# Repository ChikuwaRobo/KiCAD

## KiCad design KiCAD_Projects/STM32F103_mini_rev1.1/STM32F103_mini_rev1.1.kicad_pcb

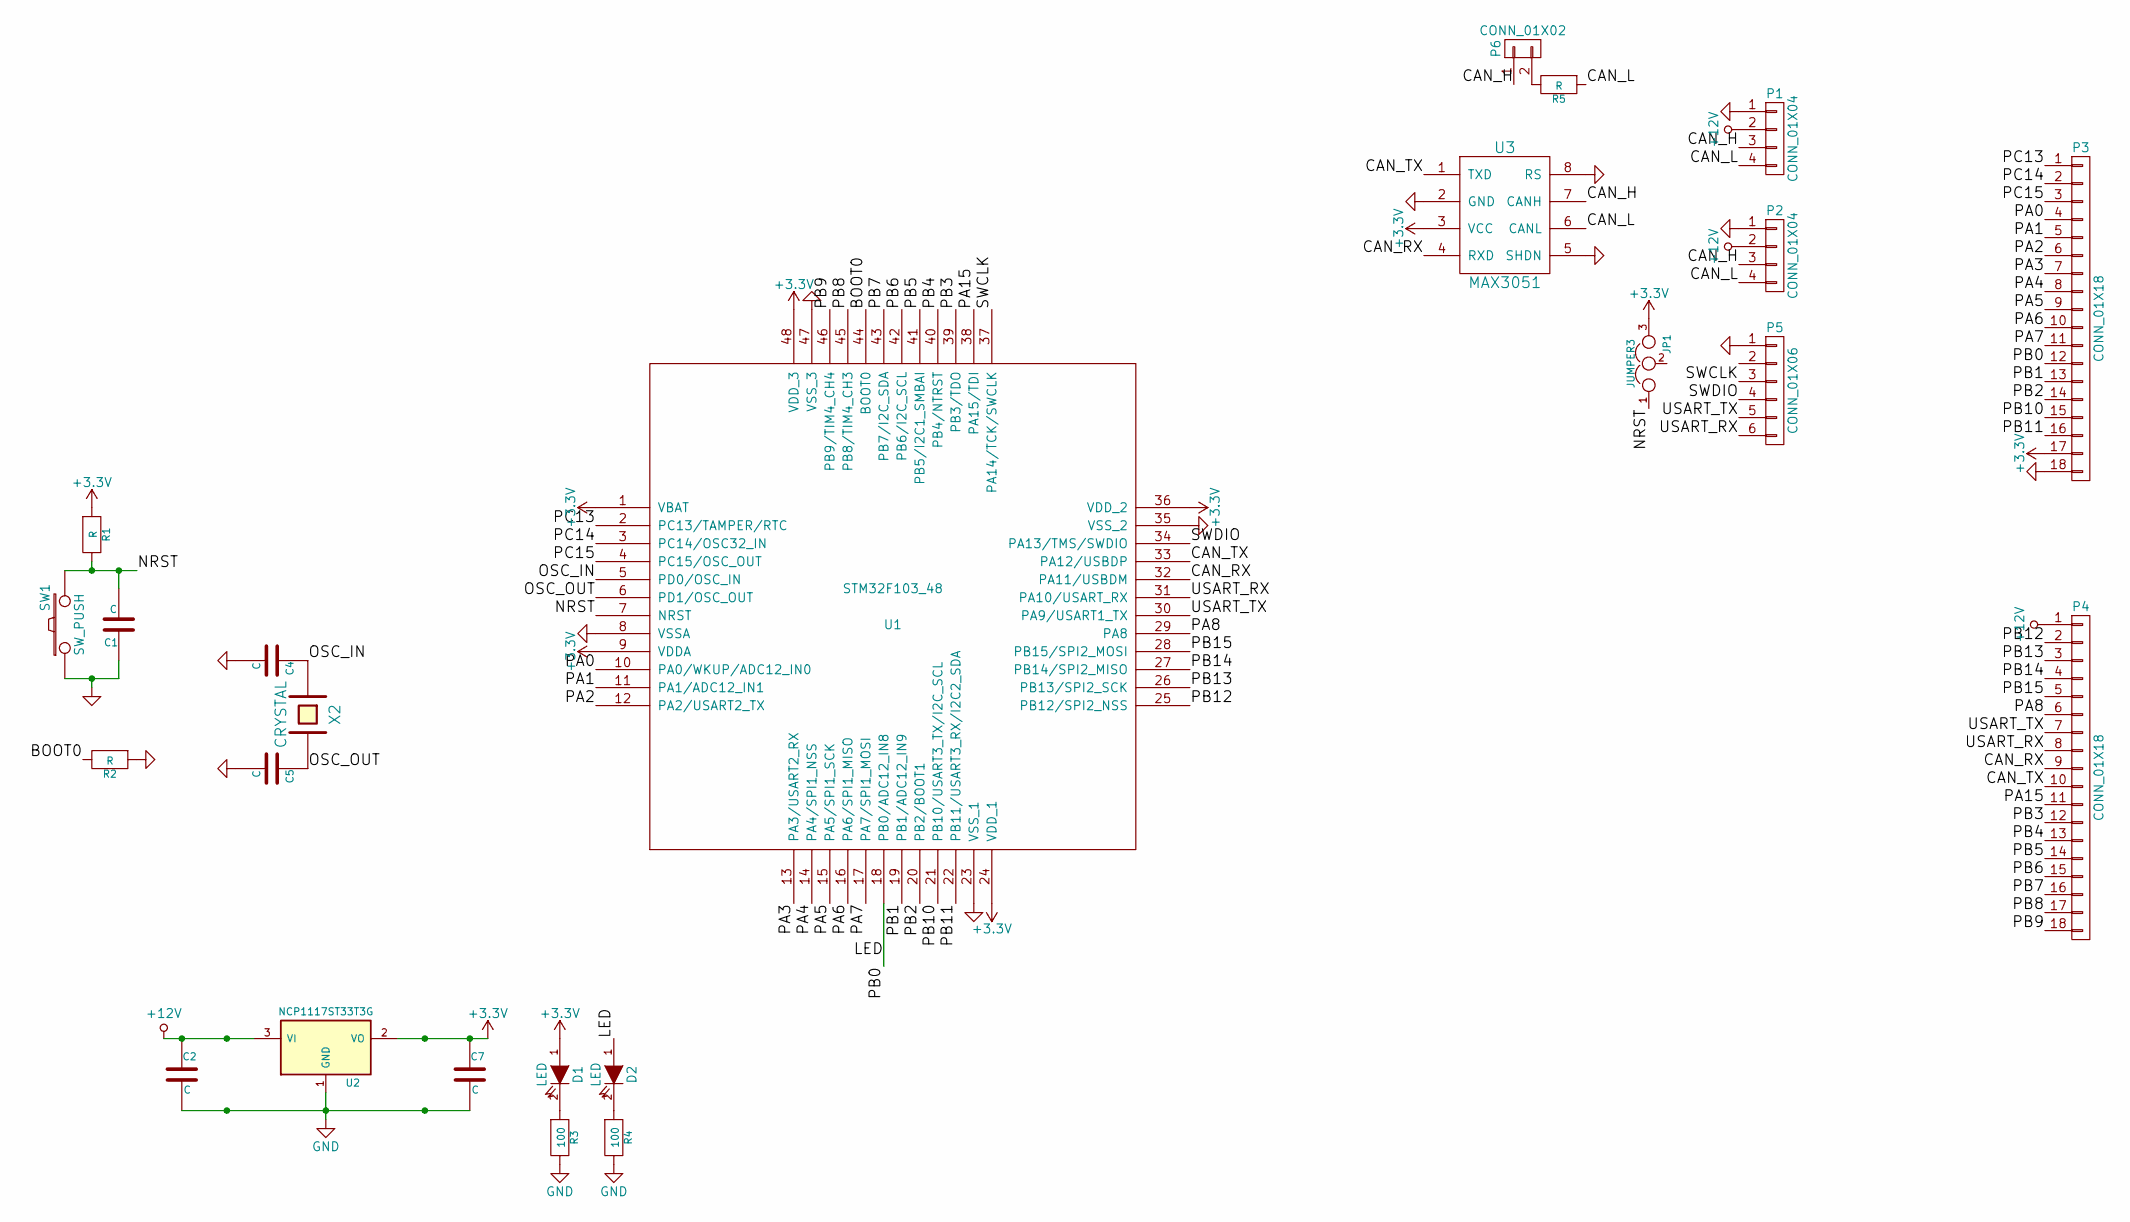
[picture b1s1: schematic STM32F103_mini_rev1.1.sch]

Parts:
C1, C2, C4, C5, C7: C; C1608_WP
D1, D2: LED; LED_0805
JP1: JUMPER3; GS3
P1, P2: CONN_01X04; XA_4LC
P3, P4: CONN_01X18; Pin_Header_Straight_1x18
P5: CONN_01X06; ZH_6T
P6: CONN_01X02; Pin_Header_Straight_1x02
R1, R2, R5: R; C1608_WP
R3, R4: 100; C1608_WP
SW1: SW_PUSH; SW_SPST_EVQPE1
U1: STM32F103_48; LQFP-48_7x7mm_Pitch0.5mm
U2: NCP1117ST33T3G; SOT-223_reg
U3: MAX3051; SOIC-8_3.9x4.9mm_Pitch1.27mm
X2: CRYSTAL; ABM3_2pads

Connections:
+3V3: C7.1, D1.1 (A), JP1.3, P3.17, R1.1, U1.1 (VBAT), U1.9 (VDDA), U1.24 (VDD_1), U1.36 (VDD_2), U1.48 (VDD_3), U2.2 (VO), U3.3 (VCC)
+12V: C2.1, P1.2, P2.2, P4.1, U2.3 (VI)
/BOOT0: R2.2, U1.44 (BOOT0)
/CAN_H: P1.3, P2.3, P6.1, U3.7 (CANH)
/CAN_L: P1.4, P2.4, R5.1, U3.6 (CANL)
/CAN_RX: P4.9, U1.32 (PA11/USBDM), U3.4 (RXD)
/CAN_TX: P4.10, U1.33 (PA12/USBDP), U3.1 (TXD)
/LED: D2.1 (A), P3.12, U1.18 (PB0/ADC12_IN8)
/NRST: C1.2, JP1.1, R1.2, SW1.2, U1.7 (NRST)
/OSC_IN: C4.1, U1.5 (PD0/OSC_IN), X2.1
/OSC_OUT: C5.1, U1.6 (PD1/OSC_OUT), X2.2
/PA0: P3.4, U1.10 (PA0/WKUP/ADC12_IN0)
/PA1: P3.5, U1.11 (PA1/ADC12_IN1)
/PA2: P3.6, U1.12 (PA2/USART2_TX)
/PA3: P3.7, U1.13 (PA3/USART2_RX)
/PA4: P3.8, U1.14 (PA4/SPI1_NSS)
/PA5: P3.9, U1.15 (PA5/SPI1_SCK)
/PA6: P3.10, U1.16 (PA6/SPI1_MISO)
/PA7: P3.11, U1.17 (PA7/SPI1_MOSI)
/PA8: P4.6, U1.29 (PA8)
/PA15: P4.11, U1.38 (PA15/TDI)
/PB1: P3.13, U1.19 (PB1/ADC12_IN9)
/PB2: P3.14, U1.20 (PB2/BOOT1)
/PB3: P4.12, U1.39 (PB3/TDO)
/PB4: P4.13, U1.40 (PB4/NTRST)
/PB5: P4.14, U1.41 (PB5/I2C1_SMBAI)
/PB6: P4.15, U1.42 (PB6/I2C_SCL)
/PB7: P4.16, U1.43 (PB7/I2C_SDA)
/PB8: P4.17, U1.45 (PB8/TIM4_CH3)
/PB9: P4.18, U1.46 (PB9/TIM4_CH4)
/PB10: P3.15, U1.21 (PB10/USART3_TX/I2C_SCL)
/PB11: P3.16, U1.22 (PB11/USART3_RX/I2C2_SDA)
/PB12: P4.2, U1.25 (PB12/SPI2_NSS)
/PB13: P4.3, U1.26 (PB13/SPI2_SCK)
/PB14: P4.4, U1.27 (PB14/SPI2_MISO)
/PB15: P4.5, U1.28 (PB15/SPI2_MOSI)
/PC13: P3.1, U1.2 (PC13/TAMPER/RTC)
/PC14: P3.2, U1.3 (PC14/OSC32_IN)
/PC15: P3.3, U1.4 (PC15/OSC_OUT)
/SWCLK: P5.3, U1.37 (PA14/TCK/SWCLK)
/SWDIO: P5.4, U1.34 (PA13/TMS/SWDIO)
/USART_RX: P4.8, P5.6, U1.31 (PA10/USART_RX)
/USART_TX: P4.7, P5.5, U1.30 (PA9/USART1_TX)
GND: C1.1, C2.2, C4.2, C5.2, C7.2, P1.1, P2.1, P3.18, P5.1, R2.1, R3.2, R4.2, SW1.1, U1.8 (VSSA), U1.23 (VSS_1), U1.35 (VSS_2), U1.47 (VSS_3), U2.1 (GND), U3.2 (GND), U3.5 (SHDN), U3.8 (RS)
unnamed: D1.2 (K), R3.1
unnamed: D2.2 (K), R4.1
unnamed: P6.2, R5.2

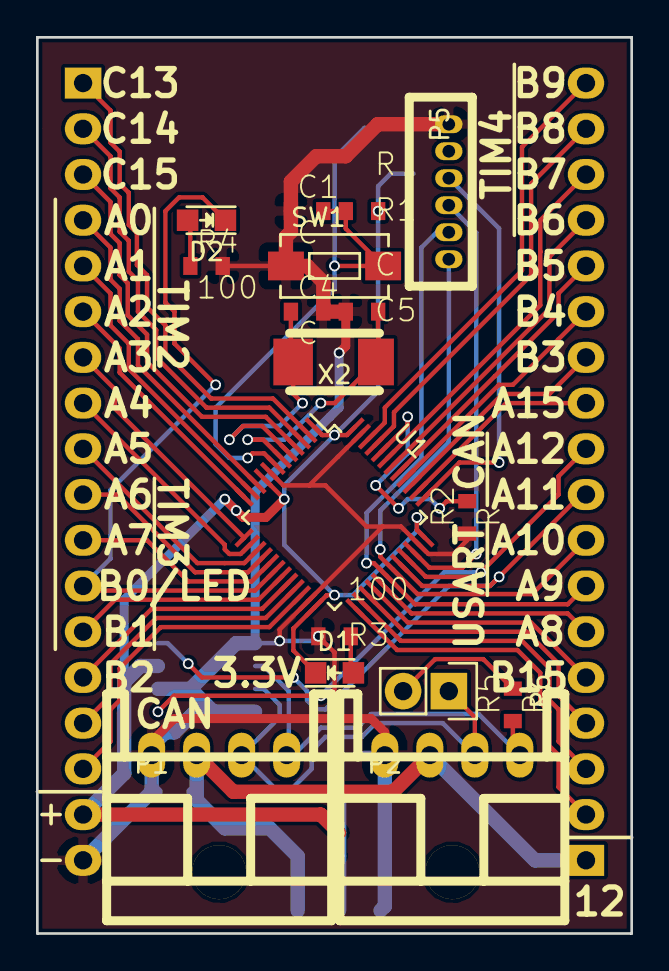
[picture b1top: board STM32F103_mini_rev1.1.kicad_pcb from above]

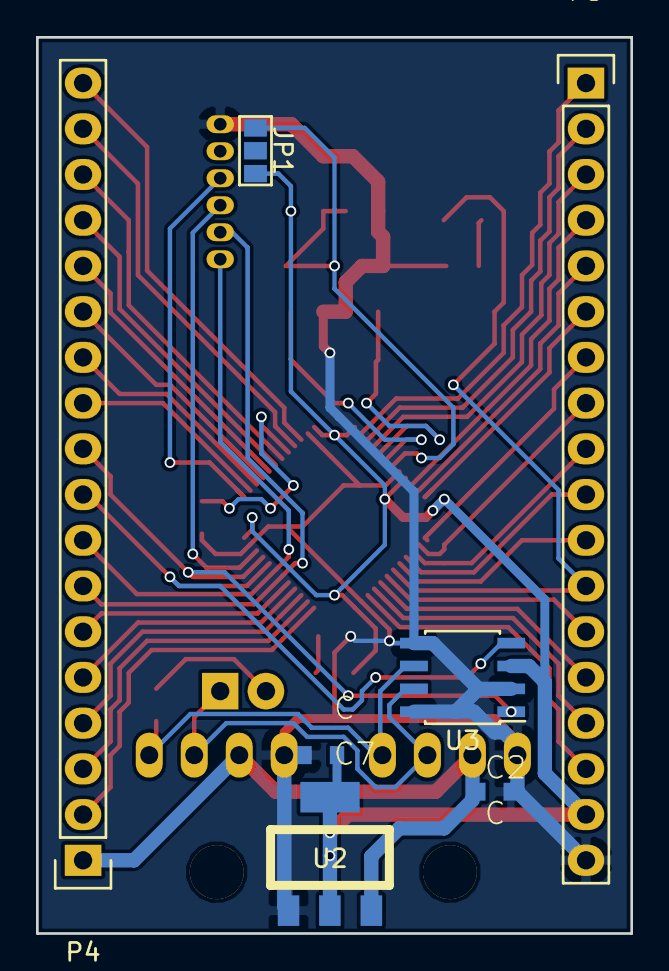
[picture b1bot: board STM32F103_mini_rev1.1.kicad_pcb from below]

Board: 2 copper layers, 33.0 x 49.8 mm, 24 parts (7 on the bottom side), 47 nets.

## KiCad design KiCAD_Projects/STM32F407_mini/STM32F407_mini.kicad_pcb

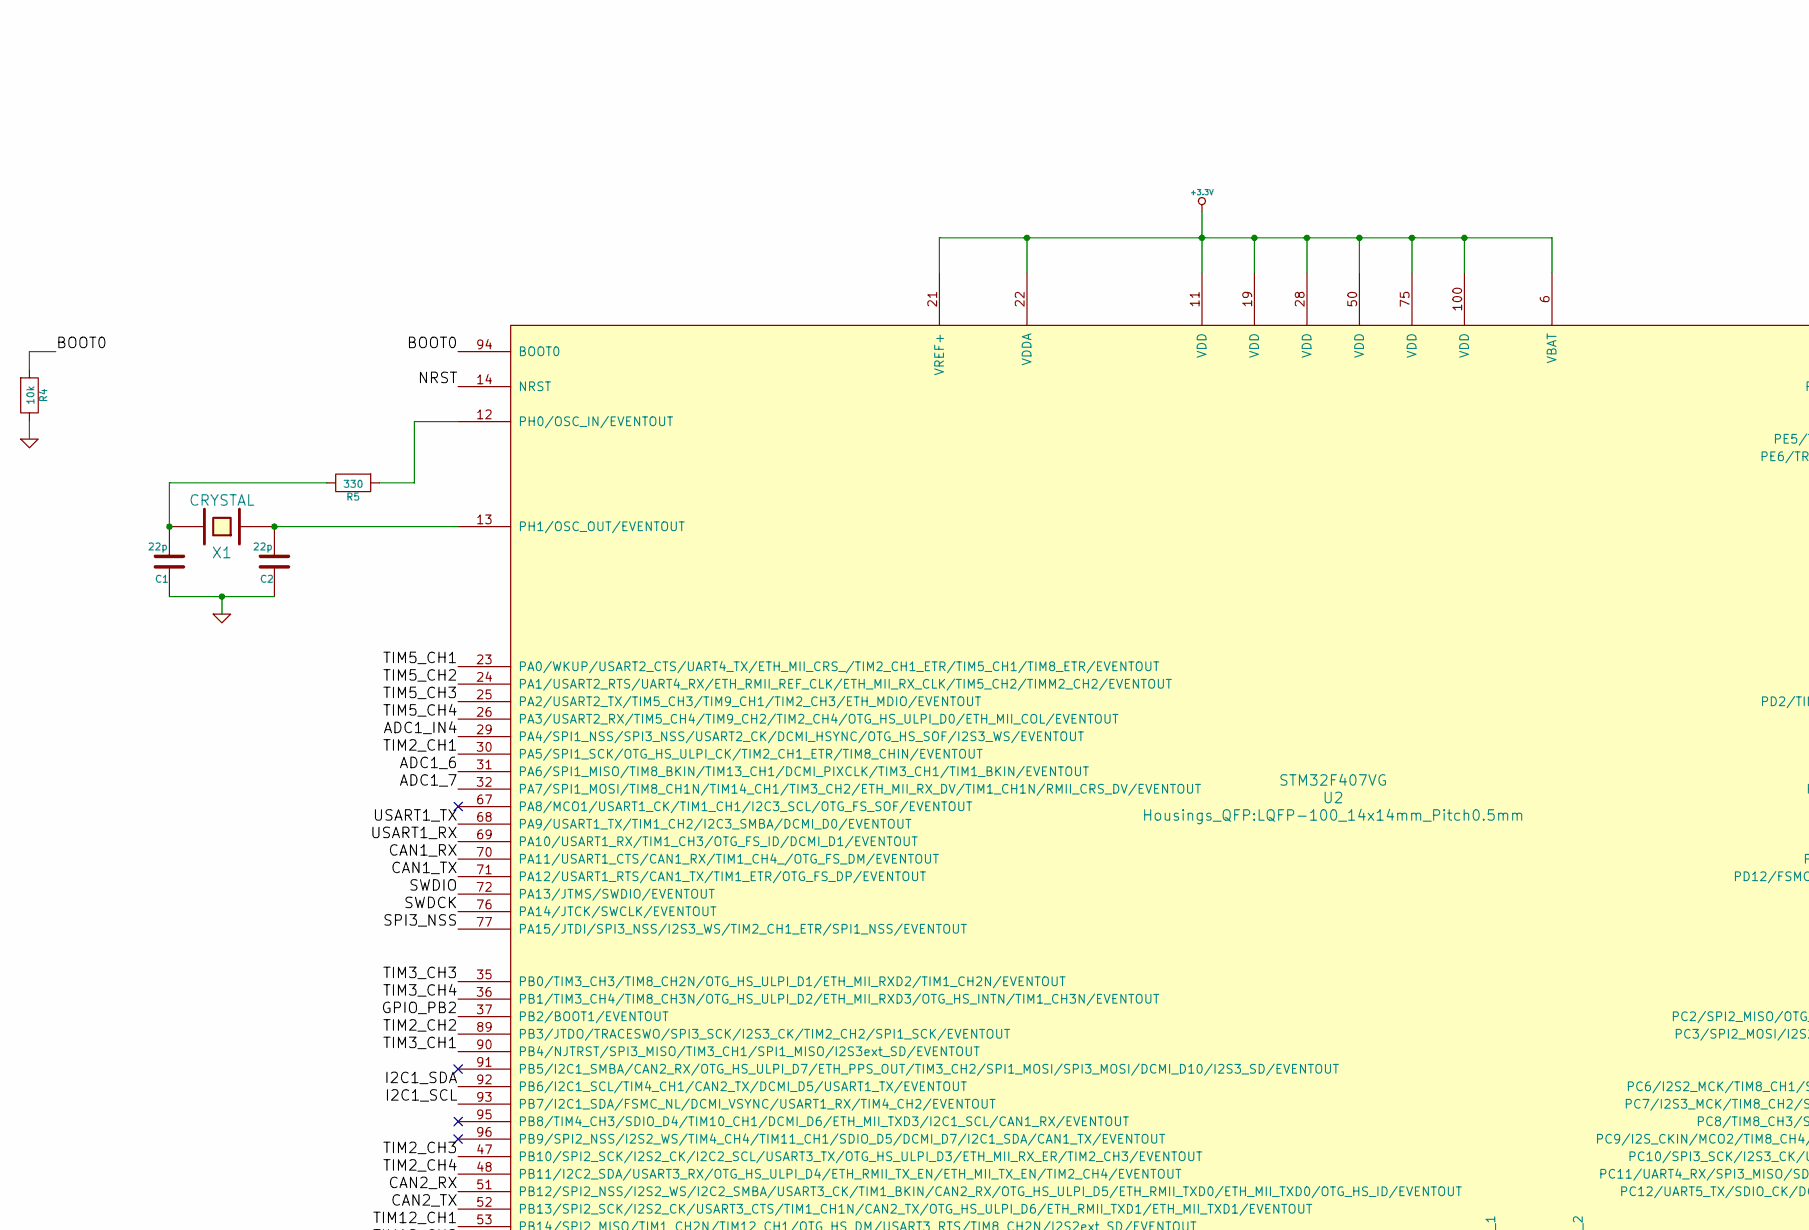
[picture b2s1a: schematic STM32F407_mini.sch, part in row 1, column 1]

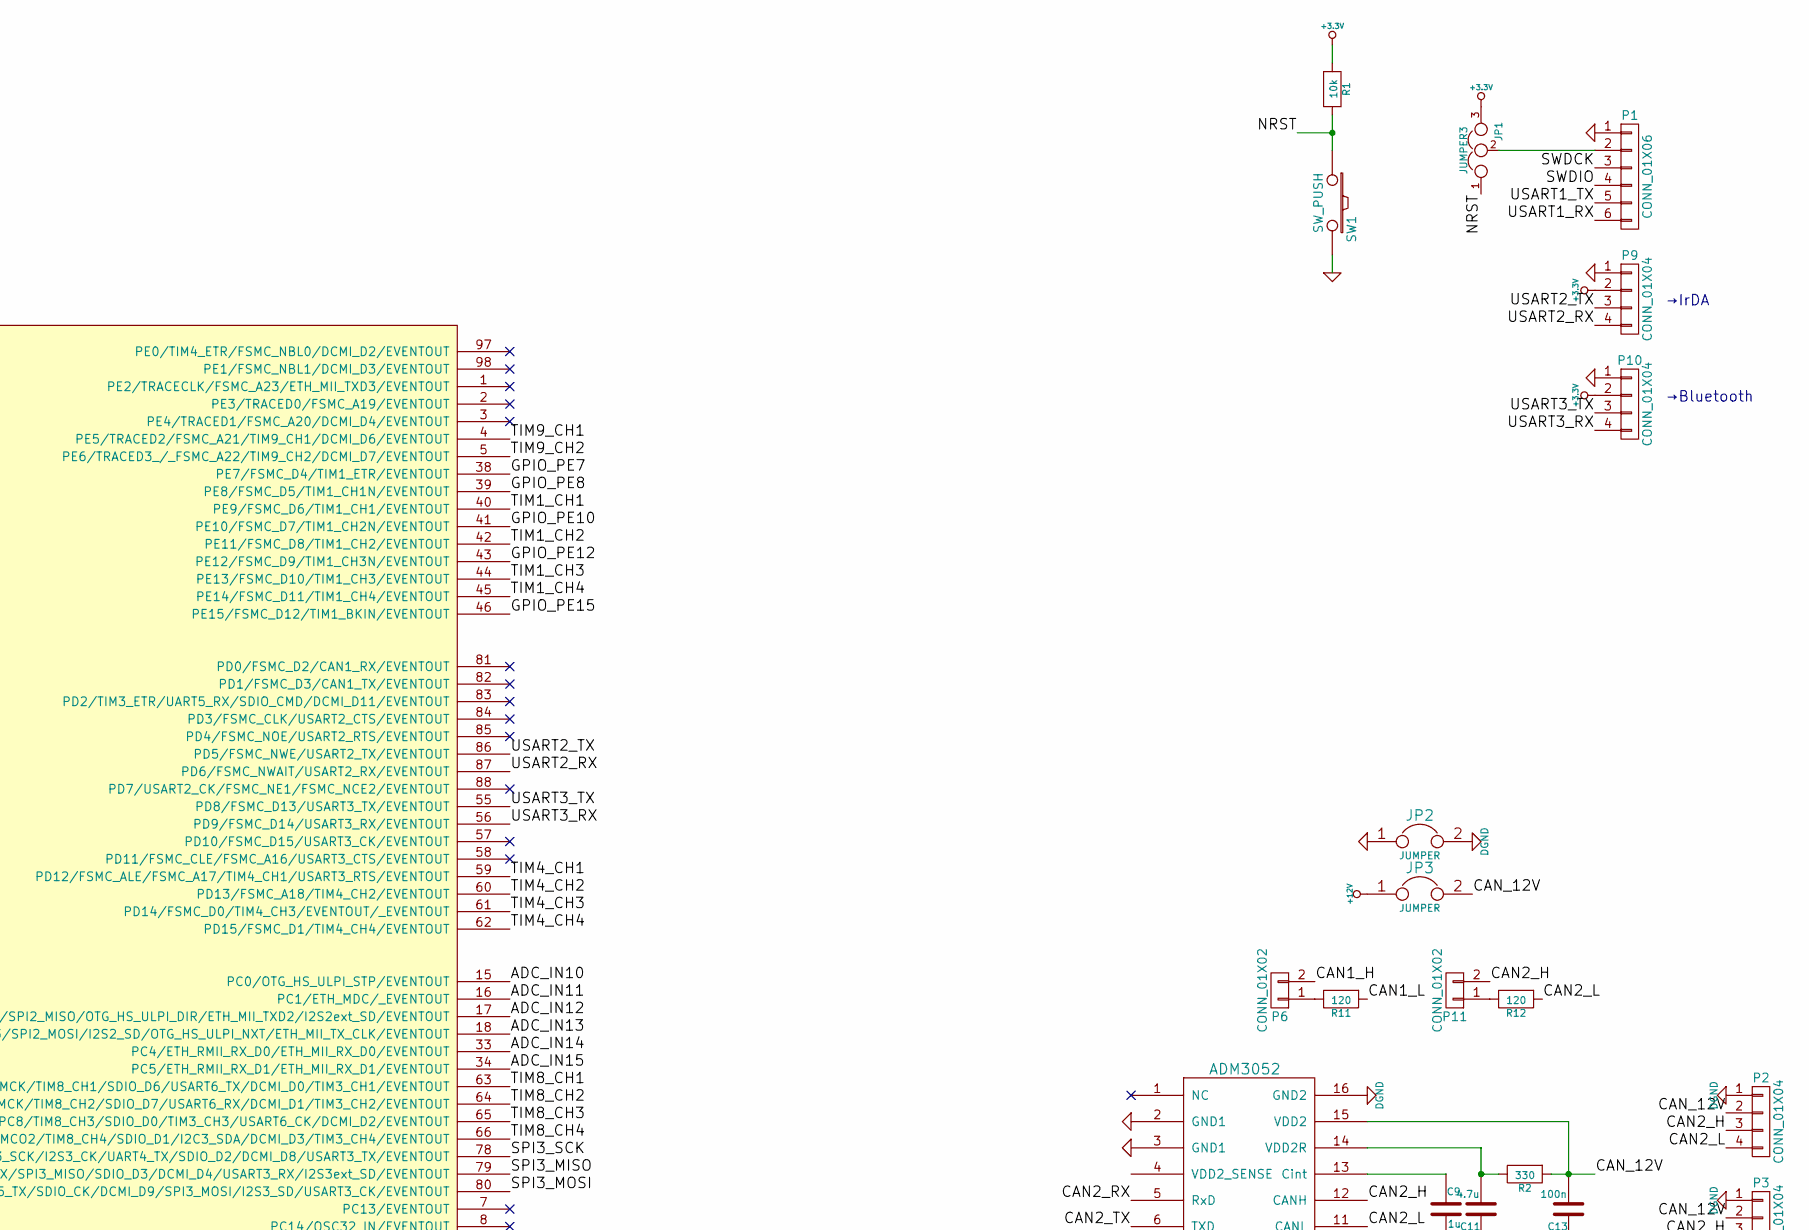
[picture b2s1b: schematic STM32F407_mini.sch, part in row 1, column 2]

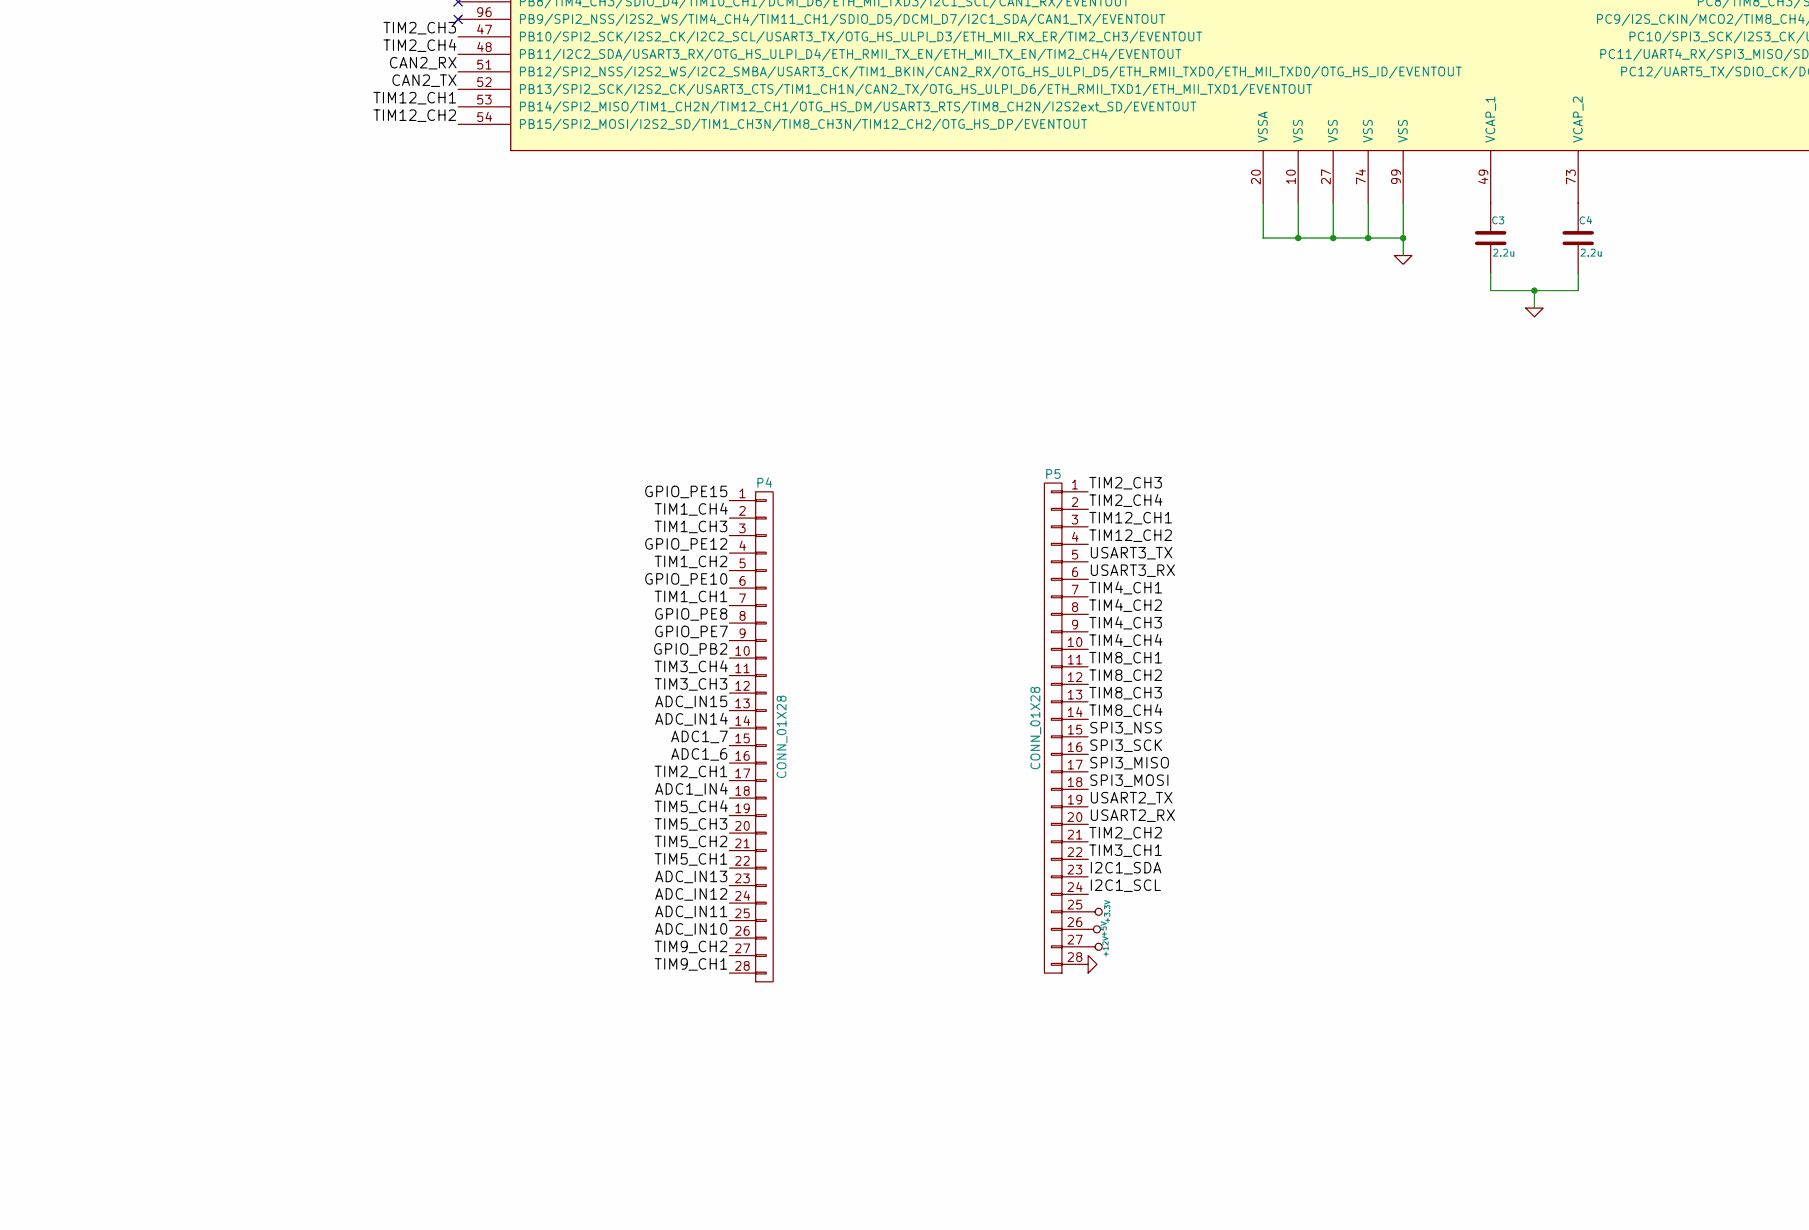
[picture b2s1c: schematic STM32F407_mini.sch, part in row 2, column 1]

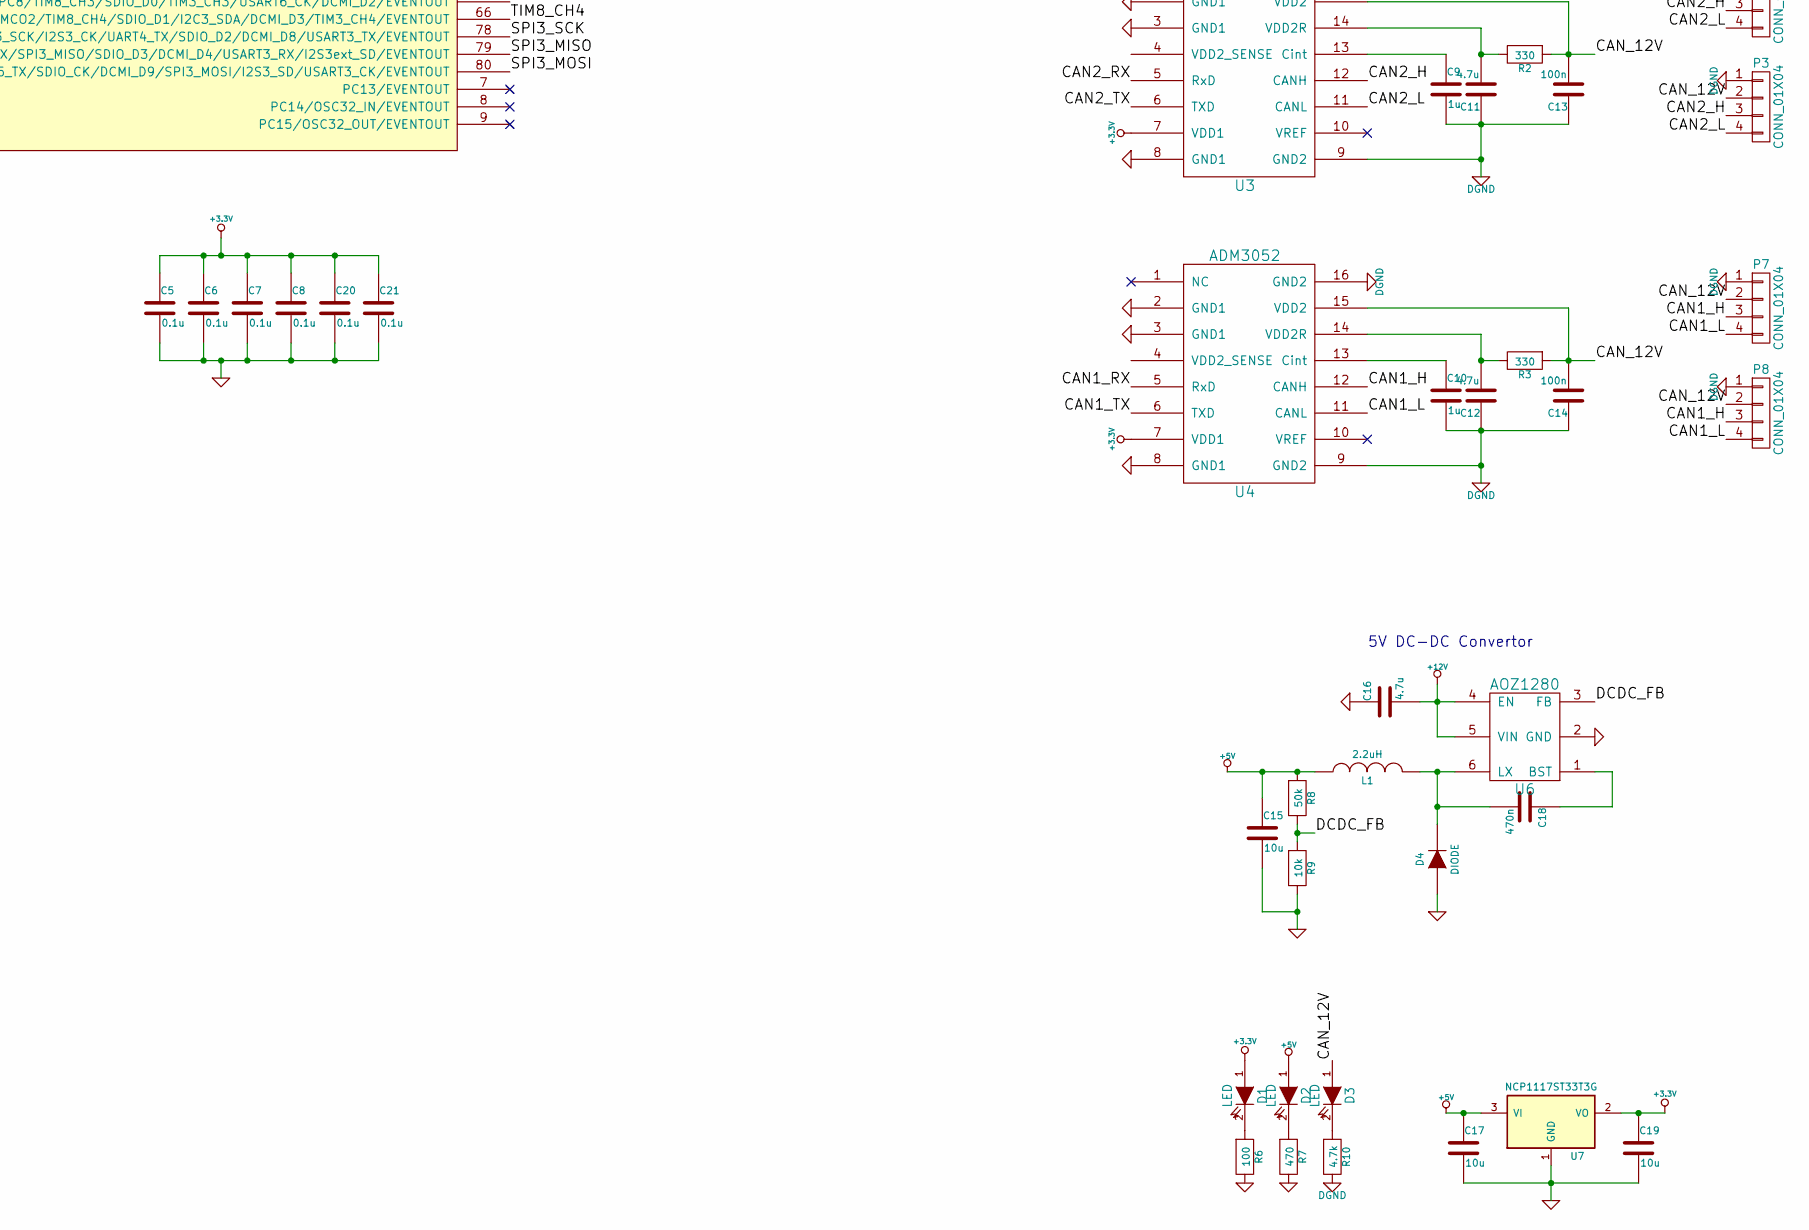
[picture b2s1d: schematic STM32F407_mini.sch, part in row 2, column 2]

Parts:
C1, C2: 22p; C1608_WP
C3, C4: 2.2u; C2012
C5, C6, C7, C8, C20, C21: 0.1u; C1608_WP
C9, C10: 1u; C2012
C11, C12, C16: 4.7u; C3216
C13, C14: 100n; C1608_WP
C15, C17, C19: 10u; C3216
C18: 470n; C1608_WP
D1, D2, D3: LED; C1608_WP
D4: DIODE; C3216
JP1: JUMPER3; GS3
JP2, JP3: JUMPER; GS2
L1: 2.2uH; Choke_SMD_6.3x6.3_H3
P1: CONN_01X06; ZH_6T
P2, P8, P9, P10: CONN_01X04; XA_4T
P3, P7: CONN_01X04; XA_4LC
P4, P5: CONN_01X28; Pin_Header_Straight_1x28
P6, P11: CONN_01X02; Pin_Header_Straight_1x02
R1, R4, R9: 10k; C1608_WP
R2, R3: 330; C3216
R5: 330; C1608_WP
R6: 100; C1608_WP
R7: 470; C1608_WP
R8: 50k; C1608_WP
R10: 4.7k; C1608_WP
R11, R12: 120; C1608_WP
SW1: SW_PUSH; RP_SMD_Button
U2: STM32F407VG; LQFP-100_14x14mm_Pitch0.5mm
U3, U4: ADM3052; SOIC-16_7.5x10.3mm_Pitch1.27mm
U6: AOZ1280; SOT-23-6
U7: NCP1117ST33T3G; SOT-223_reg
X1: CRYSTAL; ABM3_2pads

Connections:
+3.3V: C5.1, C6.1, C7.1, C8.1, C19.1, C20.1, C21.1, D1.1 (A), JP1.3, P5.25, P9.2, P10.2, R1.1, U2.6 (VBAT), U2.11 (VDD), U2.19 (VDD), U2.21 (VREF+), U2.22 (VDDA), U2.28 (VDD), U2.50 (VDD), U2.75 (VDD), U2.100 (VDD), U3.7 (VDD1), U4.7 (VDD1), U7.2 (VO)
+5V: C15.1, C17.1, D2.1 (A), L1.1, P5.26, R8.1, U7.3 (VI)
+12V: C16.2, JP3.1, P5.27, U6.4 (EN), U6.5 (VIN)
/ADC1_6: P4.16, U2.31 (PA6/SPI1_MISO/TIM8_BKIN/TIM13_CH1/DCMI_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)
/ADC1_7: P4.15, U2.32 (PA7/SPI1_MOSI/TIM8_CH1N/TIM14_CH1/TIM3_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)
/ADC1_IN4: P4.18, U2.29 (PA4/SPI1_NSS/SPI3_NSS/USART2_CK/DCMI_HS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)
/ADC_IN10: P4.26, U2.15 (PC0/OTG_HS_ULPI_STP/EVENTOUT)
/ADC_IN11: P4.25, U2.16 (PC1/ETH_MDC/_EVENTOUT)
/ADC_IN12: P4.24, U2.17 (PC2/SPI2_MISO/OTG_HS_ULPI_DIR/ETH_MII_T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)
/ADC_IN13: P4.23, U2.18 (PC3/SPI2_MOSI/I2S2_SD/OTG_HS_ULPI_NXT/E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)
/ADC_IN14: P4.14, U2.33 (PC4/ETH_RMII_RX_D0/ETH_MII_RX_D0/EVENTO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)
/ADC_IN15: P4.13, U2.34 (PC5/ETH_RMII_RX_D1/ETH_MII_RX_D1/EVENTO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)
/BOOT0: R4.1, U2.94 (BOOT0)
/CAN1_H: P6.2, P7.3, P8.3, U4.12 (CANH)
/CAN1_L: P7.4, P8.4, R11.1, U4.11 (CANL)
/CAN1_RX: U2.70 (PA11/USART1_CTS/CAN1_RX/TIM1_CH4_/OTG_F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), U4.5 (RxD)
/CAN1_TX: U2.71 (PA12/USART1_RTS/CAN1_TX/TIM1_ETR/OTG_FS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), U4.6 (TXD)
/CAN2_H: P2.3, P3.3, P11.2, U3.12 (CANH)
/CAN2_L: P2.4, P3.4, R12.1, U3.11 (CANL)
/CAN2_RX: U2.51 (PB12/SPI2_NSS/I2S2_WS/I2C2_SMBA/USART3_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), U3.5 (RxD)
/CAN2_TX: U2.52 (PB13/SPI2_SCK/I2S2_CK/USART3_CTS/TIM1_C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), U3.6 (TXD)
/CAN_12V: C13.2, C14.2, D3.1 (A), JP3.2, P2.2, P3.2, P7.2, P8.2, R2.1, R3.1, U3.15 (VDD2), U4.15 (VDD2)
/DCDC_FB: R8.2, R9.1, U6.3 (FB)
/GPIO_PB2: P4.10, U2.37 (PB2/BOOT1/EVENTOUT)
/GPIO_PE7: P4.9, U2.38 (PE7/FSMC_D4/TIM1_ETR/EVENTOUT)
/GPIO_PE8: P4.8, U2.39 (PE8/FSMC_D5/TIM1_CH1N/EVENTOUT)
/GPIO_PE10: P4.6, U2.41 (PE10/FSMC_D7/TIM1_CH2N/EVENTOUT)
/GPIO_PE12: P4.4, U2.43 (PE12/FSMC_D9/TIM1_CH3N/EVENTOUT)
/GPIO_PE15: P4.1, U2.46 (PE15/FSMC_D12/TIM1_BKIN/EVENTOUT)
/I2C1_SCL: P5.24, U2.93 (PB7/I2C1_SDA/FSMC_NL/DCMI_VSYNC/USART1_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)
/I2C1_SDA: P5.23, U2.92 (PB6/I2C1_SCL/TIM4_CH1/CAN2_TX/DCMI_D5/U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)
/NRST: JP1.1, R1.2, SW1.1, U2.14 (NRST)
/SPI3_MISO: P5.17, U2.79 (PC11/UART4_RX/SPI3_MISO/SDIO_D3/DCMI_D4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)
/SPI3_MOSI: P5.18, U2.80 (PC12/UART5_TX/SDIO_CK/DCMI_D9/SPI3_MOSI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)
/SPI3_NSS: P5.15, U2.77 (PA15/JTDI/SPI3_NSS/I2S3_WS/TIM2_CH1_ETR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)
/SPI3_SCK: P5.16, U2.78 (PC10/SPI3_SCK/I2S3_CK/UART4_TX/SDIO_D2/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)
/SWDCK: P1.3, U2.76 (PA14/JTCK/SWCLK/EVENTOUT)
/SWDIO: P1.4, U2.72 (PA13/JTMS/SWDIO/EVENTOUT)
/TIM1_CH1: P4.7, U2.40 (PE9/FSMC_D6/TIM1_CH1/EVENTOUT)
/TIM1_CH2: P4.5, U2.42 (PE11/FSMC_D8/TIM1_CH2/EVENTOUT)
/TIM1_CH3: P4.3, U2.44 (PE13/FSMC_D10/TIM1_CH3/EVENTOUT)
/TIM1_CH4: P4.2, U2.45 (PE14/FSMC_D11/TIM1_CH4/EVENTOUT)
/TIM2_CH1: P4.17, U2.30 (PA5/SPI1_SCK/OTG_HS_ULPI_CK/TIM2_CH1_ET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)
/TIM2_CH2: P5.21, U2.89 (PB3/JTDO/TRACESWO/SPI3_SCK/I2S3_CK/TIM2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)
/TIM2_CH3: P5.1, U2.47 (PB10/SPI2_SCK/I2S2_CK/I2C2_SCL/USART3_T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)
/TIM2_CH4: P5.2, U2.48 (PB11/I2C2_SDA/USART3_RX/OTG_HS_ULPI_D4/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)
/TIM3_CH1: P5.22, U2.90 (PB4/NJTRST/SPI3_MISO/TIM3_CH1/SPI1_MISO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)
/TIM3_CH3: P4.12, U2.35 (PB0/TIM3_CH3/TIM8_CH2N/OTG_HS_ULPI_D1/E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)
/TIM3_CH4: P4.11, U2.36 (PB1/TIM3_CH4/TIM8_CH3N/OTG_HS_ULPI_D2/E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)
/TIM4_CH1: P5.7, U2.59 (PD12/FSMC_ALE/FSMC_A17/TIM4_CH1/USART3_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)
/TIM4_CH2: P5.8, U2.60 (PD13/FSMC_A18/TIM4_CH2/EVENTOUT)
/TIM4_CH3: P5.9, U2.61 (PD14/FSMC_D0/TIM4_CH3/EVENTOUT/_EVENTOUT)
/TIM4_CH4: P5.10, U2.62 (PD15/FSMC_D1/TIM4_CH4/EVENTOUT)
/TIM5_CH1: P4.22, U2.23 (PA0/WKUP/USART2_CTS/UART4_TX/ETH_MII_CR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)
/TIM5_CH2: P4.21, U2.24 (PA1/USART2_RTS/UART4_RX/ETH_RMII_REF_CL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)
/TIM5_CH3: P4.20, U2.25 (PA2/USART2_TX/TIM5_CH3/TIM9_CH1/TIM2_CH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)
/TIM5_CH4: P4.19, U2.26 (PA3/USART2_RX/TIM5_CH4/TIM9_CH2/TIM2_CH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)
/TIM8_CH1: P5.11, U2.63 (PC6/I2S2_MCK/TIM8_CH1/SDIO_D6/USART6_TX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)
/TIM8_CH2: P5.12, U2.64 (PC7/I2S3_MCK/TIM8_CH2/SDIO_D7/USART6_RX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)
/TIM8_CH3: P5.13, U2.65 (PC8/TIM8_CH3/SDIO_D0/TIM3_CH3/USART6_CK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)
/TIM8_CH4: P5.14, U2.66 (PC9/I2S_CKIN/MCO2/TIM8_CH4/SDIO_D1/I2C3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)
/TIM9_CH1: P4.28, U2.4 (PE5/TRACED2/FSMC_A21/TIM9_CH1/DCMI_D6/E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)
/TIM9_CH2: P4.27, U2.5 (PE6/TRACED3_/_FSMC_A22/TIM9_CH2/DCMI_D7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)
/TIM12_CH1: P5.3, U2.53 (PB14/SPI2_MISO/TIM1_CH2N/TIM12_CH1/OTG_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)
/TIM12_CH2: P5.4, U2.54 (PB15/SPI2_MOSI/I2S2_SD/TIM1_CH3N/TIM8_C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)
/USART1_RX: P1.6, U2.69 (PA10/USART1_RX/TIM1_CH3/OTG_FS_ID/DCMI_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)
/USART1_TX: P1.5, U2.68 (PA9/USART1_TX/TIM1_CH2/I2C3_SMBA/DCMI_D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)
/USART2_RX: P5.20, P9.4, U2.87 (PD6/FSMC_NWAIT/USART2_RX/EVENTOUT)
/USART2_TX: P5.19, P9.3, U2.86 (PD5/FSMC_NWE/USART2_TX/EVENTOUT)
/USART3_RX: P5.6, P10.4, U2.56 (PD9/FSMC_D14/USART3_RX/EVENTOUT)
/USART3_TX: P5.5, P10.3, U2.55 (PD8/FSMC_D13/USART3_TX/EVENTOUT)
DGND: C9.2, C10.2, C11.1, C12.1, C13.1, C14.1, JP2.2, P2.1, P3.1, P7.1, P8.1, R10.2, U3.9 (GND2), U3.16 (GND2), U4.9 (GND2), U4.16 (GND2)
GND: C1.1, C2.1, C3.2, C4.2, C5.2, C6.2, C7.2, C8.2, C15.2, C16.1, C17.2, C19.2, C20.2, C21.2, D4.2 (A), JP2.1, P1.1, P5.28, P9.1, P10.1, R4.2, R6.2, R7.2, R9.2, SW1.2, U2.10 (VSS), U2.20 (VSSA), U2.27 (VSS), U2.74 (VSS), U2.99 (VSS), U3.2 (GND1), U3.3 (GND1), U3.8 (GND1), U4.2 (GND1), U4.3 (GND1), U4.8 (GND1), U6.2 (GND), U7.1 (GND)
unnamed: C1.2, R5.2, X1.2
unnamed: C2.2, U2.13 (PH1/OSC_OUT/EVENTOUT), X1.1
unnamed: C3.1, U2.49 (VCAP_1)
unnamed: C4.1, U2.73 (VCAP_2)
unnamed: C9.1, U3.13 (Cint)
unnamed: C10.1, U4.13 (Cint)
unnamed: C11.2, R2.2, U3.14 (VDD2R)
unnamed: C12.2, R3.2, U4.14 (VDD2R)
unnamed: C18.1, U6.1 (BST)
unnamed: C18.2, D4.1 (K), L1.2, U6.6 (LX)
unnamed: D1.2 (K), R6.1
unnamed: D2.2 (K), R7.1
unnamed: D3.2 (K), R10.1
unnamed: JP1.2, P1.2
unnamed: P6.1, R11.2
unnamed: P11.1, R12.2
unnamed: R5.1, U2.12 (PH0/OSC_IN/EVENTOUT)

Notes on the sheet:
→IrDA
→Bluetooth
5V DC-DC Convertor

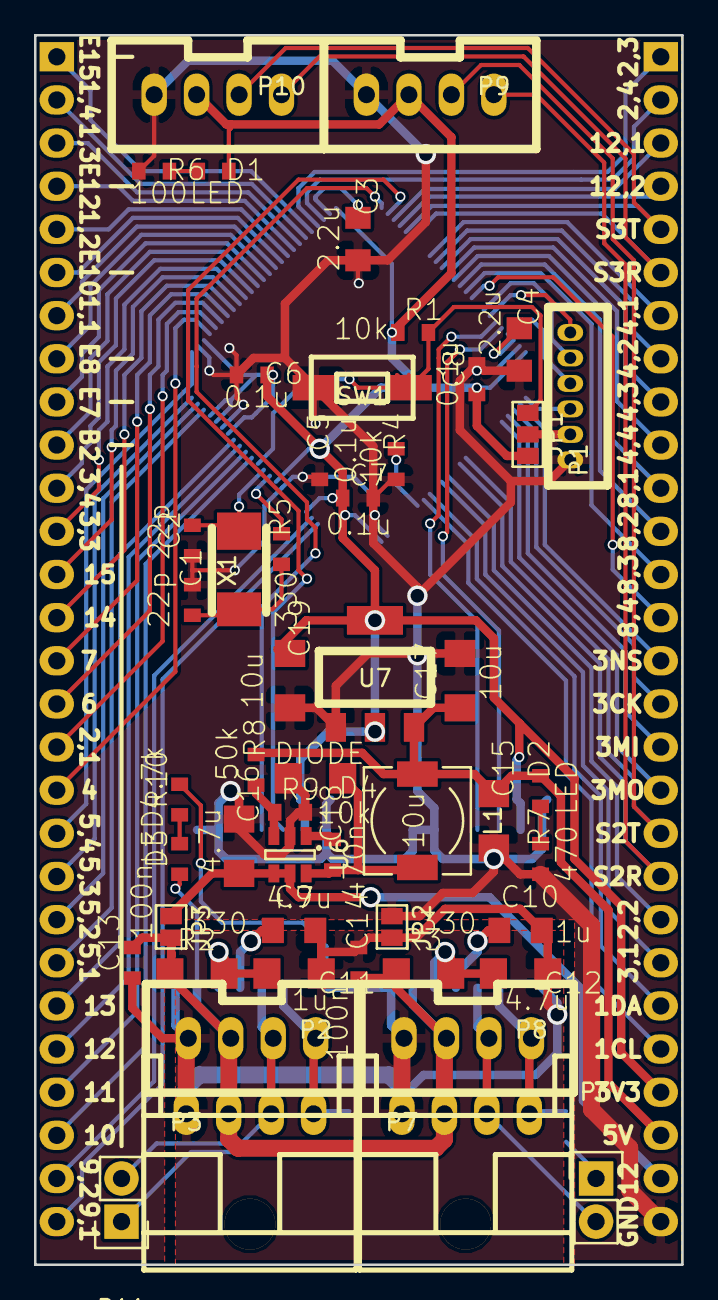
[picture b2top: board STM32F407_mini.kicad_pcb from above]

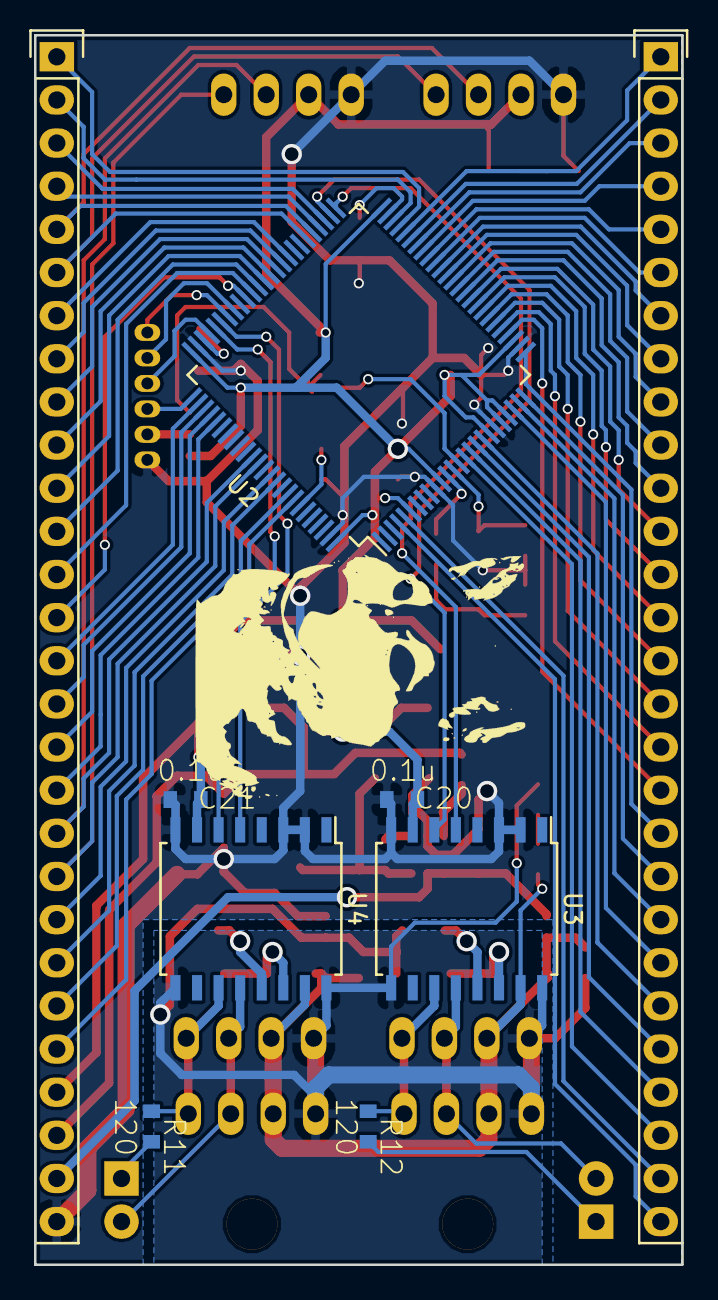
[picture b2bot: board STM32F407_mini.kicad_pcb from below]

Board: 2 copper layers, 38.1 x 72.4 mm, 59 parts (9 on the bottom side), 90 nets.
